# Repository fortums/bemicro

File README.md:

<h1>Bemicro</h1>
A macropad designed for Hackclub's Stardance.<br>
This is a half macropad half beatmania controller inspired by the <a href="https://github.com/ianklug/bemini">Bemini</a>.<br>
This was started on the 12th, and is now concluding on the 21st. not too bad for a first hardware project, if i do say so myself.<br>

AI FREE!!
<br><br>
<h2>the board itself</h2>
This was probably the most fun part. <br>
The keys (including the encoder button) are wired in a matrix with diodes. Theres 4 Neopixel LEDs in a row, A rotary encoder, and a small OLED screen.
<br> Every pin of the Xiao RP2040 is used except for the 3.3v pin, which is unneeded here.<br>

<br>
wiring it was also pretty fun, but not as much, it was a lot of doing and then redoing.<br>
i ended up with this masterfully (horribly) wired board<br>

<br>
which looks like this in the 3d view<br>

<br><br>
<h2>The case!</h2>
its really bare bones. The Xiao, leds, keyswitches, and roatary encoder all need to be left (mostly) uncovered, so theres not much to really add a top over, so theres no top. for now.(if i feel its needed once its built, i will make one.)
<br><br>
notably, the encoder knob (to mirror a beatmania controller) looks like a tunrtable... kinda. its that odd shape so that it can still be spin-able dj style, but also not cover the whole board.<br>
<br>
the board screws into the case (with the keyswitches facing "south" and the indent in the case facing "north"). the "turntable" friction fits over the D shaft of the rotary encoder.
<h2>qmk...</h2>
man qmk was a headache. it was quite the process to get rolling, mostly the guide was not at all for this usecase. but, with some perseverance and a bit of luck i figured it out.<br>
the default keybinds are as follows.<br>
  S,  D,  F,   ESC(on rotary encoder)<br>
Z,  X,  C,  V<br><br>
The rotary encoder itself types G on a counter clockwise turn and B on a clockwise turn <br>
holding the rotary encoder button also enables the led control layer, for as long as you hold it.<br>
the binds are <br>
       Hue up,    Sat up,    Val up,    ____(you should be holding this anyways)<br>
hue down,  sat down,   val down,    toggle underglow.<br>
there isnt yet a "macro"pad layer, but there will be in the future.<br><br>
<h1>bill of materials</h1>
1x Seeed Studio Xiao RP2040<br>
8x Through-hole 1N4148 diodes<br>
7x MX-style keyswitches<br>
1x EC11E rotary encoder (the kind with a switch)<br>
1x .91 inch OLED display<br>
7x MX keycaps (white in this case)<br>
2x M3x16mm screws<br>
2x M3x5x4mm heatset inserts.<br>
4x SK6812 MINI-E LEDs

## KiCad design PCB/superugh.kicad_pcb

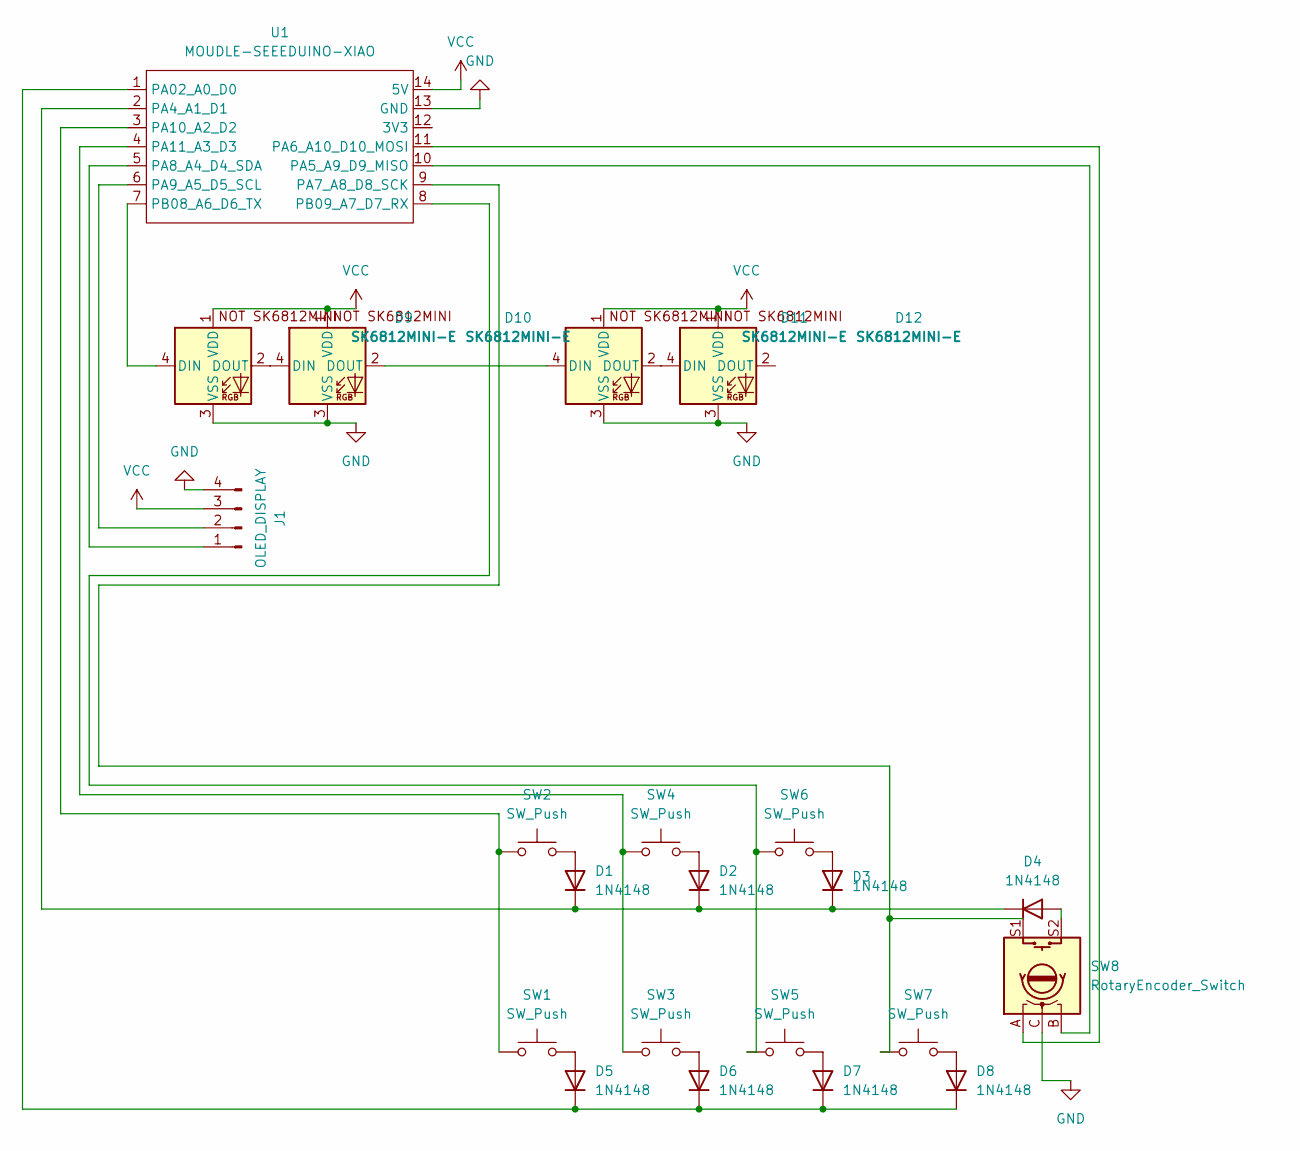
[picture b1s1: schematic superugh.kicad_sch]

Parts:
D1, D2, D3, D4, D5, D6, D7, D8: 1N4148; D_DO-35_SOD27_P7.62mm_Horizontal
D9, D10, D11, D12: SK6812MINI-E; LED_SK6812MINI-E_3.2x2.8mm_P1.5mm_ReverseMount
J1: OLED_DISPLAY; PinHeader_1x04_P2.54mm_Vertical
SW1, SW2, SW3, SW4, SW5, SW6, SW7: SW_Push; SW_Cherry_MX_1.00u_PCB
SW8: RotaryEncoder_Switch; RotaryEncoder_Alps_EC11E-Switch_Vertical_H20mm
U1: MOUDLE-SEEEDUINO-XIAO; XIAO-Generic-Hybrid-14P-2.54-21X17.8MM

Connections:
GND: D9.3 (VSS), D10.3 (VSS), D11.3 (VSS), D12.3 (VSS), J1.4, SW8.C, U1.13 (GND)
unnamed: D1.2 (A), SW2.2
unnamed: D1.1 (K), D2.1 (K), D3.1 (K), D4.1 (K), U1.2 (PA4_A1_D1)
unnamed: D2.2 (A), SW4.2
unnamed: D3.2 (A), SW6.2
unnamed: D4.2 (A), SW8.S2
unnamed: D5.2 (A), SW1.2
unnamed: D5.1 (K), D6.1 (K), D7.1 (K), D8.1 (K), U1.1 (PA02_A0_D0)
unnamed: D6.2 (A), SW3.2
unnamed: D7.2 (A), SW5.2
unnamed: D8.2 (A), SW7.2
unnamed: D9.4 (DIN), U1.7 (PB08_A6_D6_TX)
unnamed: D9.2 (DOUT), D10.4 (DIN)
unnamed: D10.2 (DOUT), D11.4 (DIN)
unnamed: D11.2 (DOUT), D12.4 (DIN)
unnamed: J1.1, U1.5 (PA8_A4_D4_SDA)
unnamed: J1.2, U1.6 (PA9_A5_D5_SCL)
unnamed: SW8.B, U1.10 (PA5_A9_D9_MISO)
unnamed: SW8.A, U1.11 (PA6_A10_D10_MOSI)
unnamed: SW7.1, SW8.S1, U1.9 (PA7_A8_D8_SCK)
unnamed: SW1.1, SW2.1, U1.3 (PA10_A2_D2)
unnamed: SW3.1, SW4.1, U1.4 (PA11_A3_D3)
unnamed: SW5.1, SW6.1, U1.8 (PB09_A7_D7_RX)
VCC: D9.1 (VDD), D10.1 (VDD), D11.1 (VDD), D12.1 (VDD), J1.3, U1.14 (5V)

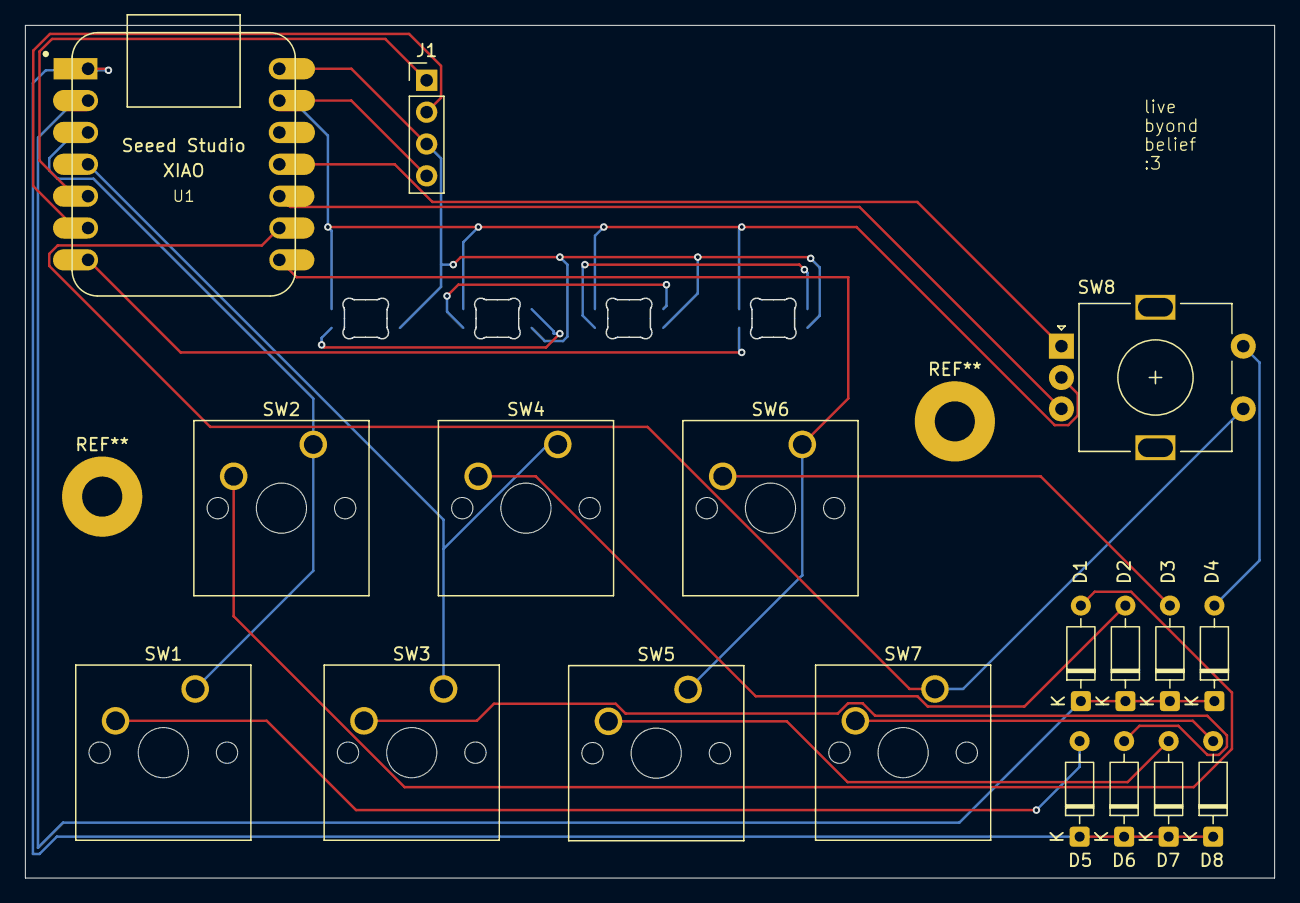
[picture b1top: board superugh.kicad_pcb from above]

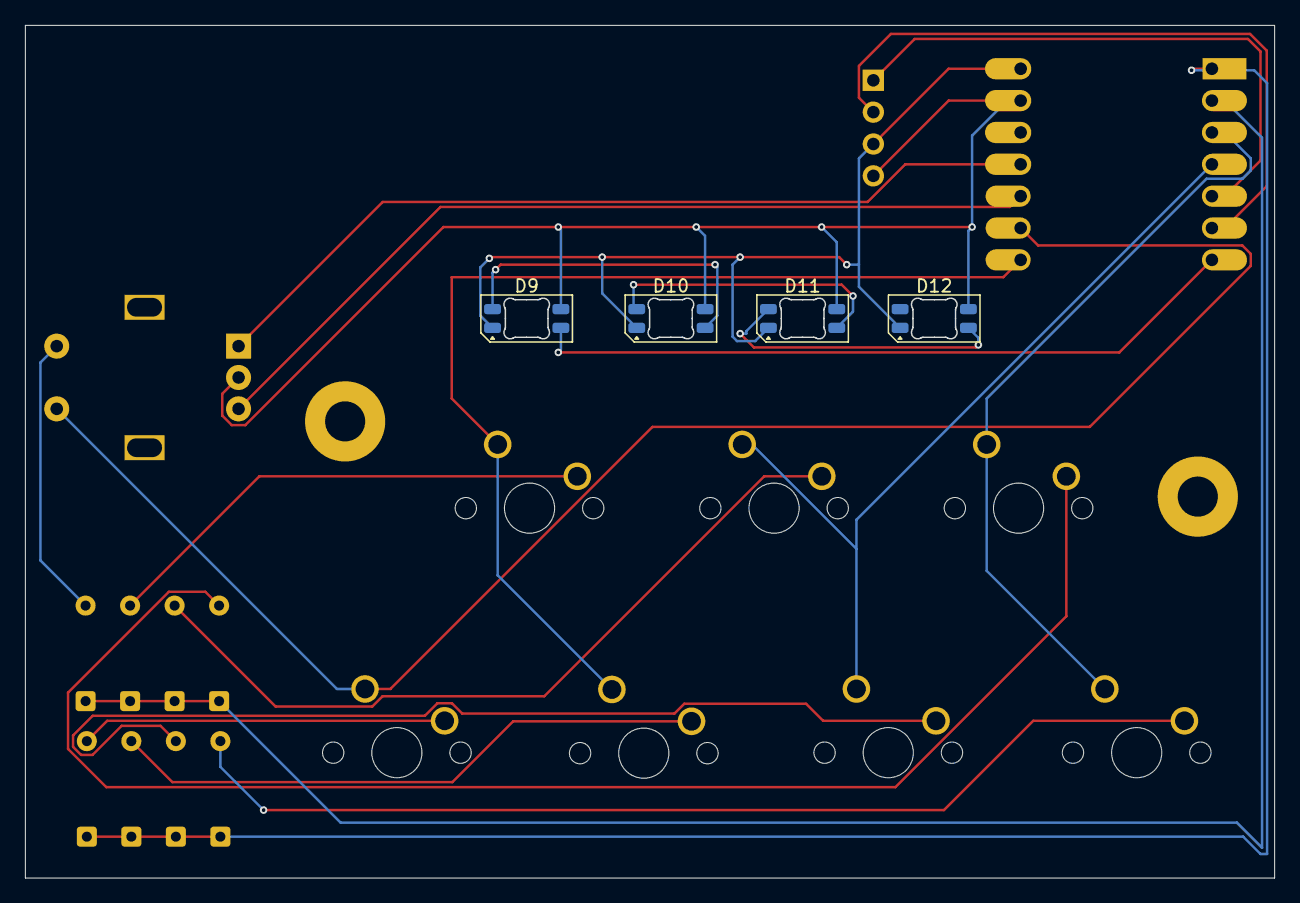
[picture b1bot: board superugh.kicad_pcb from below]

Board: 2 copper layers, 99.6 x 68.0 mm, 22 parts (4 on the bottom side), 24 nets.
